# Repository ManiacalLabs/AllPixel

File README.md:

AllPixel
========

Firmware and Board Designs for the AllPixel LED Controller Board

Be sure to check out the [AllPixel Quick Start Guide](https://github.com/ManiacalLabs/AllPixel/wiki)

The AllPixel is fully supported by the [BiblioPixel](https://github.com/ManiacalLabs/BiblioPixel) Python library

Check out our site for more details [AllPixel at Maniacal Labs](http://maniacallabs.com/products/allpixel)

The AllPixel makes use of our [ATUSB Arduino Core](https://github.com/ManiacalLabs/ATUSB_Core)

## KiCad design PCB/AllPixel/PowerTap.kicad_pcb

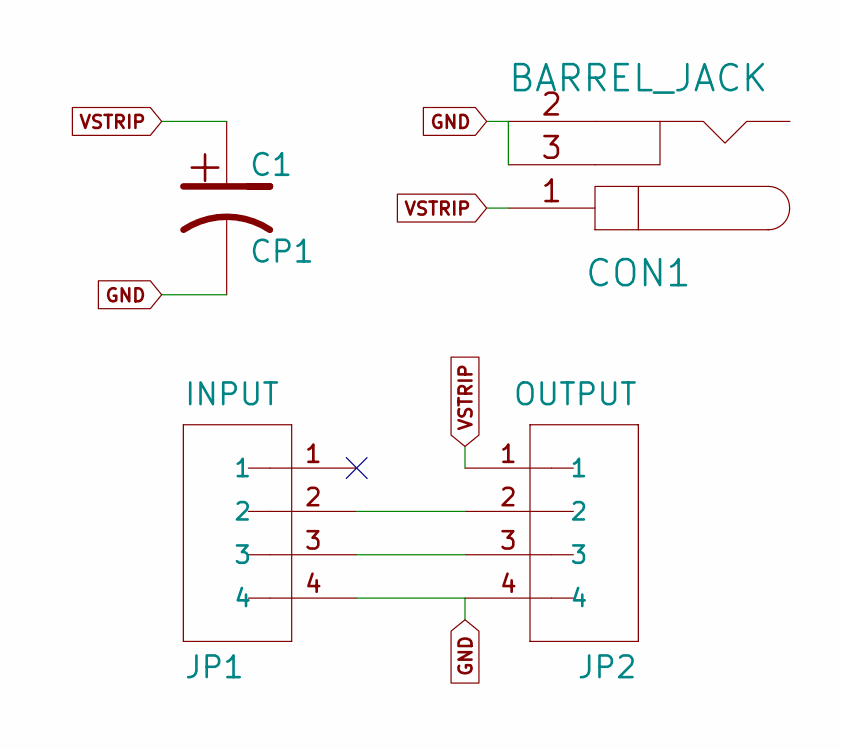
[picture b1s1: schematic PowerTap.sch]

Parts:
C1: CP1
CON1: BARREL_JACK
JP1: INPUT; SparkFun-1X04_LOCK
JP2: OUTPUT; SparkFun-1X04_LOCK

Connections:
GND: C1.2, CON1.2, CON1.3, JP1.4, JP2.4
unnamed: JP1.2, JP2.2
unnamed: JP1.3, JP2.3
VSTRIP: C1.1, CON1.1, JP2.1

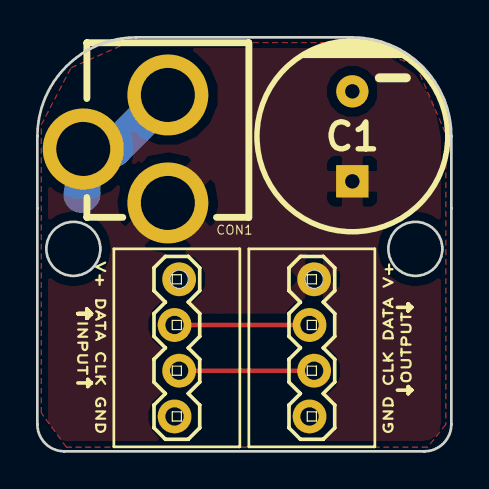
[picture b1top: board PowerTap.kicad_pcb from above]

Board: 2 copper layers, 23.0 x 23.0 mm, 4 parts (0 on the bottom side), 4 nets.

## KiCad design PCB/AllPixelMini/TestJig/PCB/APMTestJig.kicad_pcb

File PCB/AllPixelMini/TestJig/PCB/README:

Test Jig Construction:
-Used 3 layers of protoboard to allign the 4 output pogo pins
-Used 2 layers of protoboard to allign the 6 ICSP pad pins

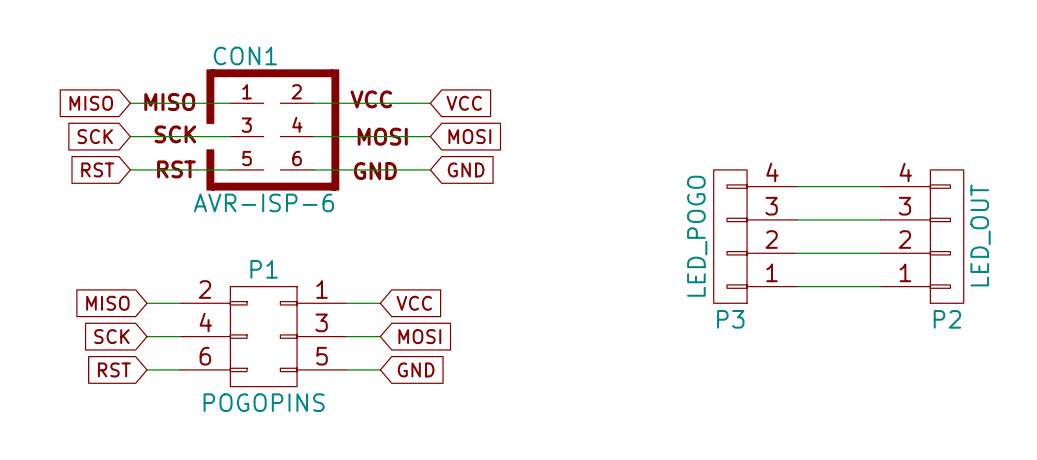
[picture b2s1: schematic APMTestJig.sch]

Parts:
CON1: AVR-ISP-6; ICSP_1mm097Drill
P1: POGOPINS; ICSP_1mm097Drill
P2: LED_OUT; TerminalBlock_Pheonix_MPT-2.54mm_4pol
P3: LED_POGO; 1x4_1mm097Drill

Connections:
GND: CON1.6, P1.5
MISO: CON1.1, P1.2
MOSI: CON1.4, P1.3
unnamed: P2.1, P3.1
unnamed: P2.2, P3.2
unnamed: P2.3, P3.3
unnamed: P2.4, P3.4
RST: CON1.5, P1.6
SCK: CON1.3, P1.4
VCC: CON1.2, P1.1

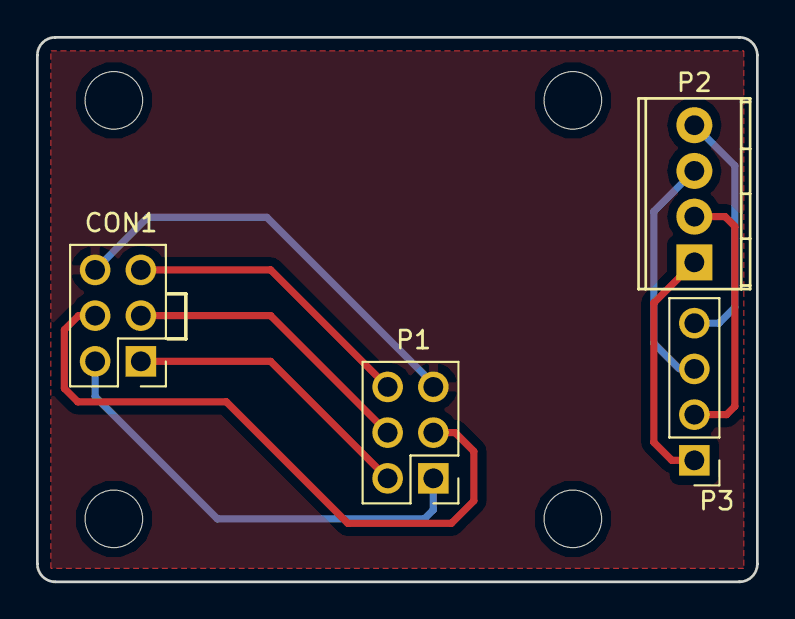
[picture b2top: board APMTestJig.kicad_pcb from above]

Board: 2 copper layers, 40.0 x 30.2 mm, 4 parts (0 on the bottom side), 10 nets.

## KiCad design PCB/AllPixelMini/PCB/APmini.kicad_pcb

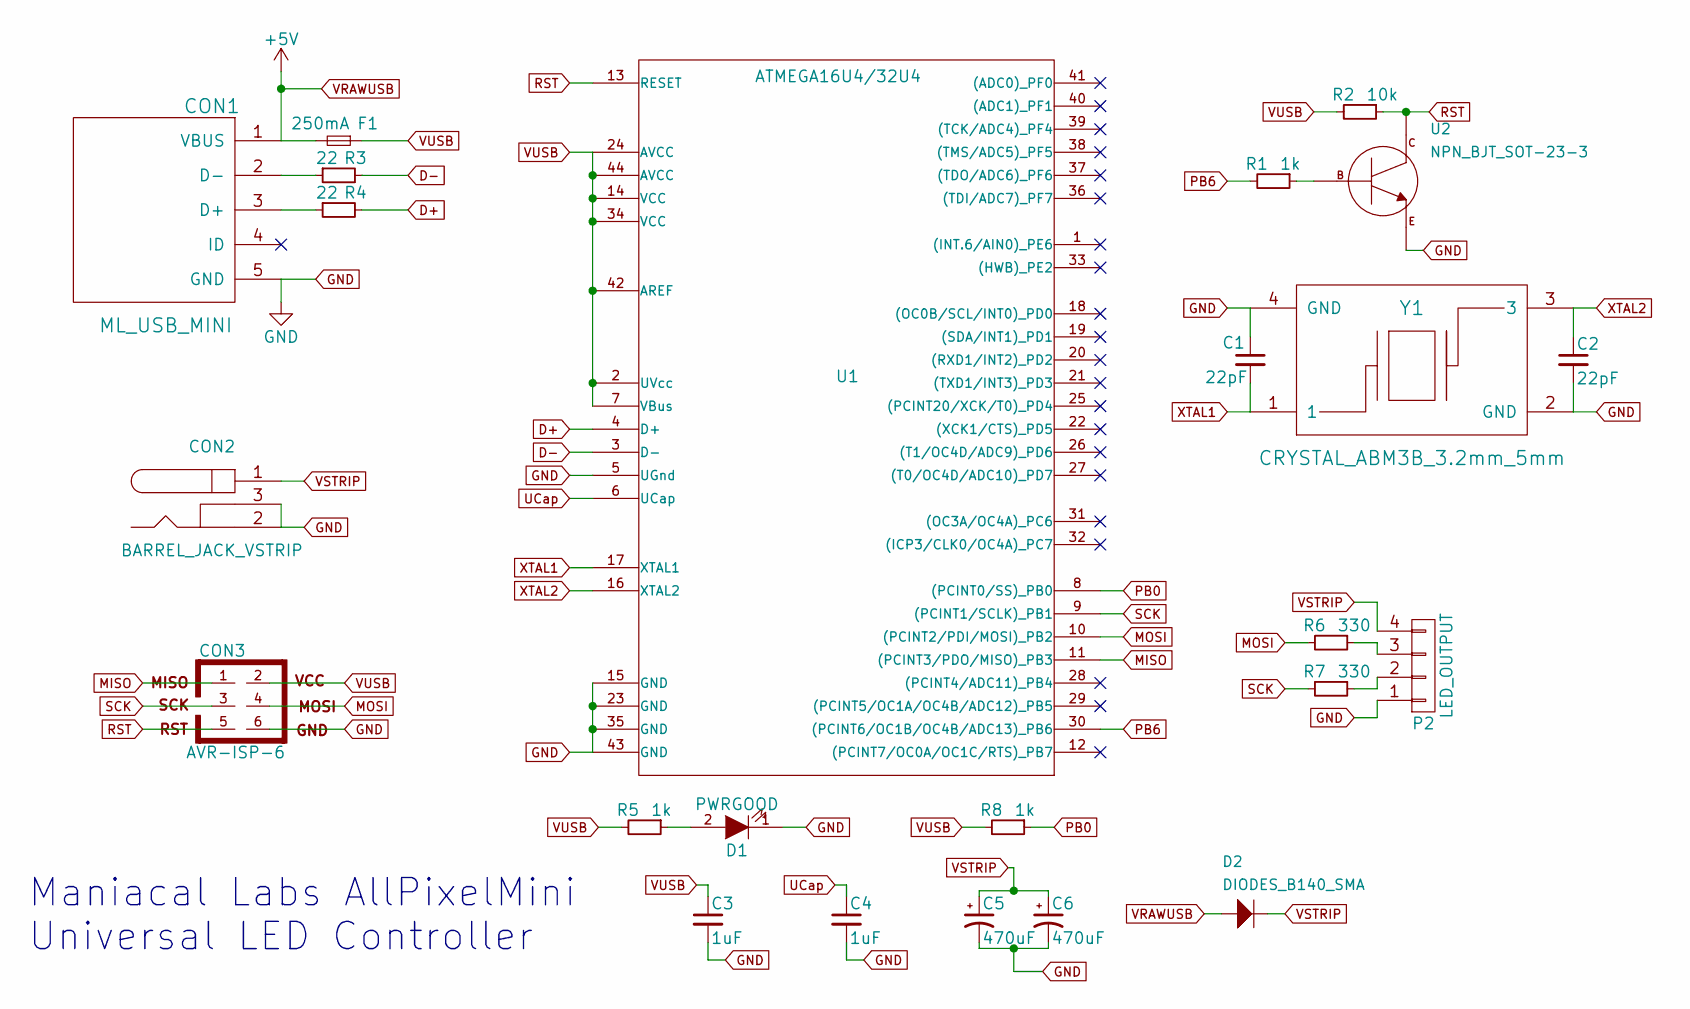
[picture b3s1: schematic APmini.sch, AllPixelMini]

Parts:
C1, C2: 22pF; C_0603
C3, C4: 1uF; C_0603
C5, C6: 470uF; c_elec_10x10
CON1: ML_USB_MINI; MF_Connectors-MICROUSB-RIGHT
CON2: BARREL_JACK_VSTRIP; ML_BARREL_JACK_ROUND_PADS_SHORT
CON3: AVR-ISP-6; ML_ICSP_PADS
D1: PWRGOOD; LED_0603
D2: DIODES_B140_SMA; MF_Discrete_Semiconductor-SMA
F1: 250mA; C_1206
P2: LED_OUTPUT; TerminalBlock_Pheonix_MPT-2.54mm_4pol
R1, R5, R8: 1k; 0603R_dist_m635
R2: 10k; 0603R_dist_m635
R3, R4: 22; 0603R_dist_m635
R6, R7: 330; 0603R_dist_m635
U1: ATMEGA16U4/32U4; TQFP-44_10x10mm_Pitch0.8mm
U2: NPN_BJT_SOT-23-3; MF_Discrete_Semiconductor-SOT-23-3
Y1: CRYSTAL_ABM3B_3.2mm_5mm; Crystal_ABM3B_3.2mm_5mm

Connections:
D+: R4.2, U1.4 (D+)
D-: R3.2, U1.3 (D-)
GND: C1.1, C2.2, C3.2, C4.2, C5.2, C6.2, CON1.5 (GND), CON2.2, CON2.3, CON3.6, D1.1 (K), P2.1, U1.5 (UGnd), U1.15 (GND), U1.23 (GND), U1.35 (GND), U1.43 (GND), U2.P$2 (EMITTER), Y1.2 (GND), Y1.4 (GND)
MISO: CON3.1, U1.11 ((PCINT3/PDO/MISO)_PB3)
MOSI: CON3.4, R6.2, U1.10 ((PCINT2/PDI/MOSI)_PB2)
unnamed: CON1.2 (D-), R3.1
unnamed: CON1.3 (D+), R4.1
unnamed: D1.2 (A), R5.1
unnamed: P2.2, R7.1
unnamed: P2.3, R6.1
unnamed: R1.1, U2.P$1 (BASE)
PB0: R8.1, U1.8 ((PCINT0/SS)_PB0)
PB6: R1.2, U1.30 ((PCINT6/OC1B/OC4B/ADC13)_PB6)
RST: CON3.5, R2.1, U1.13 (RESET), U2.P$3 (COLLECTOR)
SCK: CON3.3, R7.2, U1.9 ((PCINT1/SCLK)_PB1)
UCap: C4.1, U1.6 (UCap)
VRAWUSB: CON1.1 (VBUS), D2.ANOD (ANODE), F1.2
VSTRIP: C5.1, C6.1, CON2.1, D2.CATH (CATHODE), P2.4
VUSB: C3.1, CON3.2, F1.1, R2.2, R5.2, R8.2, U1.2 (UVcc), U1.7 (VBus), U1.14 (VCC), U1.24 (AVCC), U1.34 (VCC), U1.42 (AREF), U1.44 (AVCC)
XTAL1: C1.2, U1.17 (XTAL1), Y1.1
XTAL2: C2.1, U1.16 (XTAL2), Y1.3

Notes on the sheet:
Maniacal Labs AllPixelMini Universal LED Controller

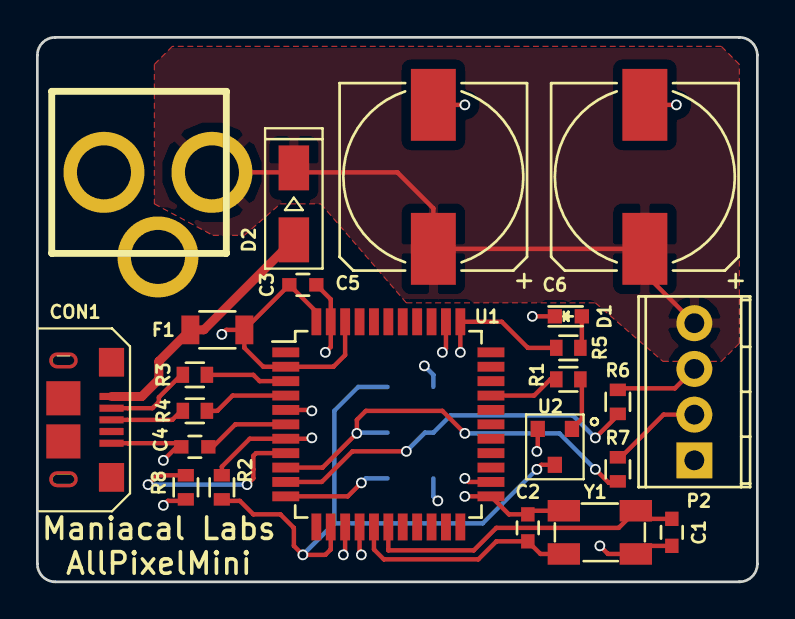
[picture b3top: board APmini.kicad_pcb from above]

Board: 4 copper layers, 40.0 x 30.2 mm, 25 parts (1 on the bottom side), 21 nets.

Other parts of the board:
L103: Maniacal Labs; logo_MLlabs

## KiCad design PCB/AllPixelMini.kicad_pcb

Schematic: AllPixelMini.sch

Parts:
C1, C2: 22pF; AXIAL-5MM
C3, C4: 1uF; AXIAL-5MM
C5: CP1
CON1: ML_USB_MINI
D1: LED
D2: DIODE
F1: 500mA
JP1: PT_OUTPUT; SparkFun-1X04_LOCK
JP2: OUTPUT; SparkFun-1X04_LOCK
JP3: PT_INPUT; SparkFun-1X04_LOCK
P1, P2: CONN_1
P3: CONN_2
Q1: NPN
R1, R5, R8: 1K; R-AXIAL-0.4
R2: 10k; R-AXIAL-0.4
R3, R4: 22; R-AXIAL-0.4
R6, R7: OPT; R-AXIAL-0.4
U1: ATMEGA16U4/32U4
Y1: 16MHz; SparkFun-HC49US

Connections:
+5V: CON1.1 (VBUS), F1.1
CLK: JP1.3, JP2.3, JP3.3, R7.2
D+: R4.1, U1.4 (D+)
D-: R3.1, U1.3 (D-)
DATA: JP1.2, JP2.2, JP3.2, R6.2
GND: C1.1, C2.2, C3.1, C4.1, C5.2, CON1.5 (GND), D1.2 (K), JP1.4, JP2.4, JP3.4, P3.1, Q1.1 (E), U1.5 (UGnd), U1.15 (GND), U1.23 (GND), U1.35 (GND), U1.43 (GND)
MISO: P1.1, U1.11 ((PCINT3/PDO/MISO)_PB3)
MOSI: R6.1, U1.10 ((PCINT2/PDI/MOSI)_PB2)
unnamed: D1.1 (A), R5.2
unnamed: Q1.2 (B), R1.1
unnamed: R8.1, U1.8 ((PCINT0/SS)_PB0)
unnamed: CON1.2 (D-), R3.2
unnamed: CON1.3 (D+), R4.2
PB6: R1.2, U1.30 ((PCINT6/OC1B/OC4B/ADC13)_PB6)
RST: P2.1, Q1.3 (C), R2.1, U1.13 (RESET)
SCK: R7.1, U1.9 ((PCINT1/SCLK)_PB1)
UCap: C4.2, U1.6 (UCap)
VJACK: C5.1, JP1.1, P3.2 (PM)
VSTRIP: D2.2 (K), JP2.1
VUSB: C3.2, D2.1 (A), F1.2, R2.2, R5.1, R8.2, U1.2 (UVcc), U1.7 (VBus), U1.14 (VCC), U1.24 (AVCC), U1.34 (VCC), U1.42 (AREF), U1.44 (AVCC)
XTAL1: C1.2, U1.17 (XTAL1), Y1.1
XTAL2: C2.1, U1.16 (XTAL2), Y1.2

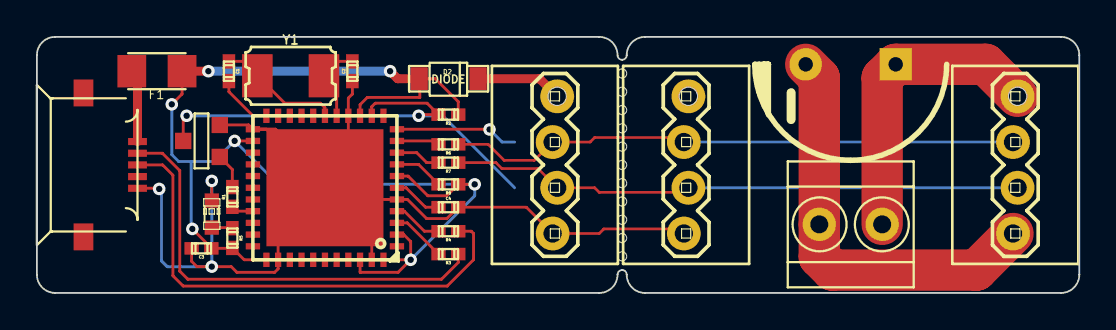
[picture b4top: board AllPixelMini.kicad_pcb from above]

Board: 2 copper layers, 57.9 x 14.2 mm, 37 parts (0 on the bottom side), 22 nets.

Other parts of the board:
20mil_drill, 20mil_drill#2, 20mil_drill#3, 20mil_drill#4, 20mil_drill#5, 20mil_drill#6, 20mil_drill#7, 20mil_drill#8, 20mil_drill#9, 20mil_drill#10, 20mil_drill#11: VAL**; 20mil_drill

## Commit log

2014-11-08 Create LICENSE
2014-11-09 Added Schematic PDF
2014-11-10 Create FastLED_LICENSE
2014-11-28 Upgraded to FastLED 3.0.3
    Added new chipsets
2014-11-28 Pulled FastLED License back in
2014-12-07 updated silkscreen
2014-12-13 better handling of not enough data being sent.
    increased pixel limit
2014-12-22 added device ID
2015-01-02 Changes to AllPixel PCB for DFM.
    Added USB connector with positioning holes (created new module).
    Flipped fuse to simplify traces.
    Enlarged holes on diode (created new module).
    Replaced Ground fix trace with standard width trace (no longer have
    smaller trace just for that one bodge).
    Cleaned up traces in a few spots to get rid of small, oddly angled
2015-01-02 More Changes to AllPixel and PowerTap for DFM
    AP: added silk labels for components
    AP: minor trace tweak on USB data pin to avoid right angle
    PT: fixed ground trace too long
2015-01-02 Fixed Crystal footprint not showing reference
    AP: Created new crystal footprint that has the reference on the top of
    the board.
2015-01-03 AP: Added labels to power jack and output pins
    AP: Added labels to power jack and output pins
    PT: Reran gerber file output. Didn't really need to, just to verify.
2015-01-03 Saved Project file.
2015-01-04 fixed silk screen on pads
2015-01-04 further fixing of silk screen
2015-01-04 fixed jack silk screen on powertap
2015-01-04 new top silk gerber
2015-01-04 Adjusted top silk. should be ready for OSHPark
2015-01-08 added hex file
2015-01-09 Modified USB footprint to center anchor.
    AP: Modified USB footprint to center anchor.
    AP: Generated position file for SMD components
2015-02-24 added driver
2015-03-14 Added Case Design
2015-03-15 Case top without hole
2015-03-22 Added TinyTim Stand
    Created TinyTiMAllPixelStand folder, added 123D Design file and stl
    export.
2015-04-08 Modified Jack and Switch Ftprnt, Fixed Via Issue
    Changed barrel jack footprint (3.5mm holes), changed switch pad spacing
    (5.5mm), fixed ground vias so that DRC passes with no unconnected pads
    and ground fill works correctly. Also added small trace between ICSP GND
    and ATMega pin 5 (think this was UGND?)
2015-04-08 Adjusted via locations to avoid footprint silkscrn
    Moved some vias to keep them away from front silk items (our logo, the
    crystal).
    Did test plot and upload to OSHPark to verify gerber files
2015-04-11 Added Rev B to bottom Left, Sent to OSHPark
    Added Rev B to bottom Left, Sent to OSHPark
2015-04-24 Working with FastLED 3.1
2015-04-25 Working on Mini AP
2015-04-25 Mini Gerbers
2015-04-26 Adding Device Version Command
2015-05-01 tweaked mini layout
2015-06-02 Working smartmatrix firmware
2015-08-26 Adding Boot/Idle Mode
2015-09-30 working on it...
2015-10-22 testing
2016-01-09 Full 16x64 and tests
2016-01-09 R/G/B/W/O animation
2016-03-05 Finalizing WyoManiacal Firmware
2016-11-12 removing SmartMatrix Ref
2017-01-30 Complete rework for Arduino 1.6 and FastLED 3.1
2017-06-18 Moving AP files to AP folder, adding APM files
2020-01-03 Fix link to AllPixel product page
